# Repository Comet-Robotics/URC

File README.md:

# UTD University Rover Challenge

This is where all of our code and most of the project management will be base at.

## Overview

Discussions: Where all research topics will go and where you will log your ideas, progress, and questions at. I will also post research materials there too.

Issues: Once research is done we will create an issue for a topic and this is where you will contribute your code too and discuss issues that are arriving in the implementation.

## Instructions
- Start up the simulation and press play. 

- In another terminal, cd to rtab_package (such a dumb name we can definitely change this) which is in the ws_urc src folder, colcon build, source the install. 
- To run, "ros2 launch rtab_package rtab.launch.py". 
  - This node takes care of all transforms needed for the Nav2 stack.
  - rgbd odometry creates an odom -> base_link odometry message
  - ukf robot_localization fuses the IMU odometry with the visual odometry and publishes the odom -> base_link transformation
  - rgbd-slam publishes the map -> odom frame
  - RTAB-MAP frame to frame model
 
- Then, cd to navigation, which is also in the ws_urc src folder. Colcon build, source the install.
  - Run with "ros2 launch navigation nav.launch.py"
  - This initializes the nav2 stack, nothing outputs after initialization unless a goal is given
 
- Start rviz2
  - Set the global frame to "map"
  - include "Robot Description" topic to see the robot (the wheels dont move with it even though the transforms are being published, don't know what's going on there)
  - Include "odometry" topic, set ros2 topic to "odometry/filtered" to see the fused odometry
  - Include "/map" topic (this doesn't show up until nav2 is activated)
  - Include "goal pose" to see the given goal
  - Go to panels, click on navigation2. It should say the navigation is active. 
  - To send actions to the robot, in rviz, select 2d goal pose and place it on the map. Click Start Waypoint Navigation in the nav2 panel to start navigation

Install git 

git clone <github_uri>

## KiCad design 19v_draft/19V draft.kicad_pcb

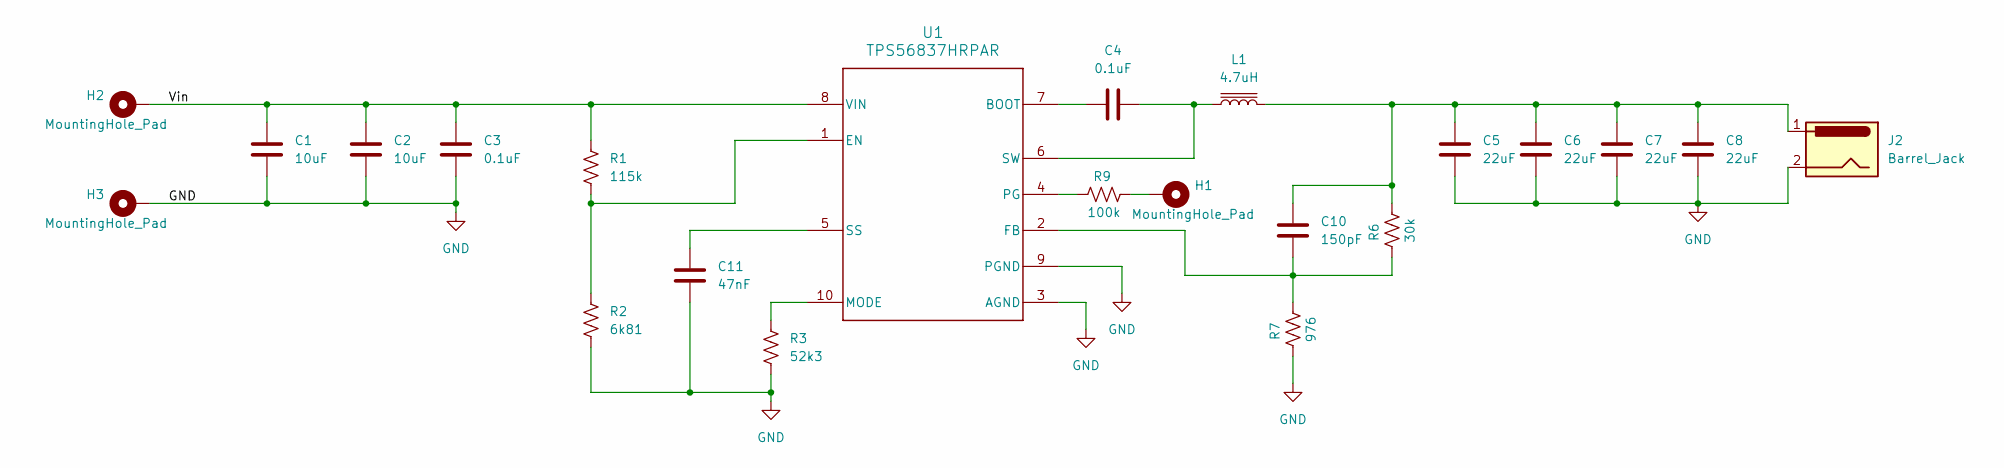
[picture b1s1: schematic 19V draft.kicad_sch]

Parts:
C1, C2: 10uF; C_0603_1608Metric
C3, C4: 0.1uF; C_0603_1608Metric
C5, C6, C7, C8: 22uF; C_0603_1608Metric
C10: 150pF; C_0603_1608Metric
C11: 47nF; C_0603_1608Metric
H1, H2, H3: MountingHole_Pad; MountingHole_2.5mm_Pad
J2: Barrel_Jack; BarrelJack_SwitchcraftConxall_RAPC10U_Horizontal
L1: 4.7uH; L_Abracon_ASPI-0630LR
R1: 115k; R_2512_6332Metric
R2: 6k81; R_2512_6332Metric
R3: 52k3; R_2512_6332Metric
R6: 30k; R_0805_2012Metric
R7: 976; R_2512_6332Metric
R9: 100k; R_0805_2012Metric
U1: TPS56837HRPAR; RPA0010A-MFG

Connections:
/Vin: C1.1, C2.1, C3.1, H2.1, R1.1, U1.8 (VIN)
GND: C1.2, C2.2, C3.2, C5.2, C6.2, C7.2, C8.2, C11.2, H3.1, J2.2, R2.2, R3.2, R7.1, U1.3 (AGND), U1.9 (PGND)
unnamed: C5.1, C6.1, C7.1, C8.1, C10.1, J2.1, L1.2, R6.2
unnamed: H1.1, R9.2
unnamed: C4.1, U1.7 (BOOT)
unnamed: R1.2, R2.1, U1.1 (EN)
unnamed: C10.2, R6.1, R7.2, U1.2 (FB)
unnamed: R3.1, U1.10 (MODE)
unnamed: R9.1, U1.4 (PG)
unnamed: C11.1, U1.5 (SS)
unnamed: C4.2, L1.1, U1.6 (SW)

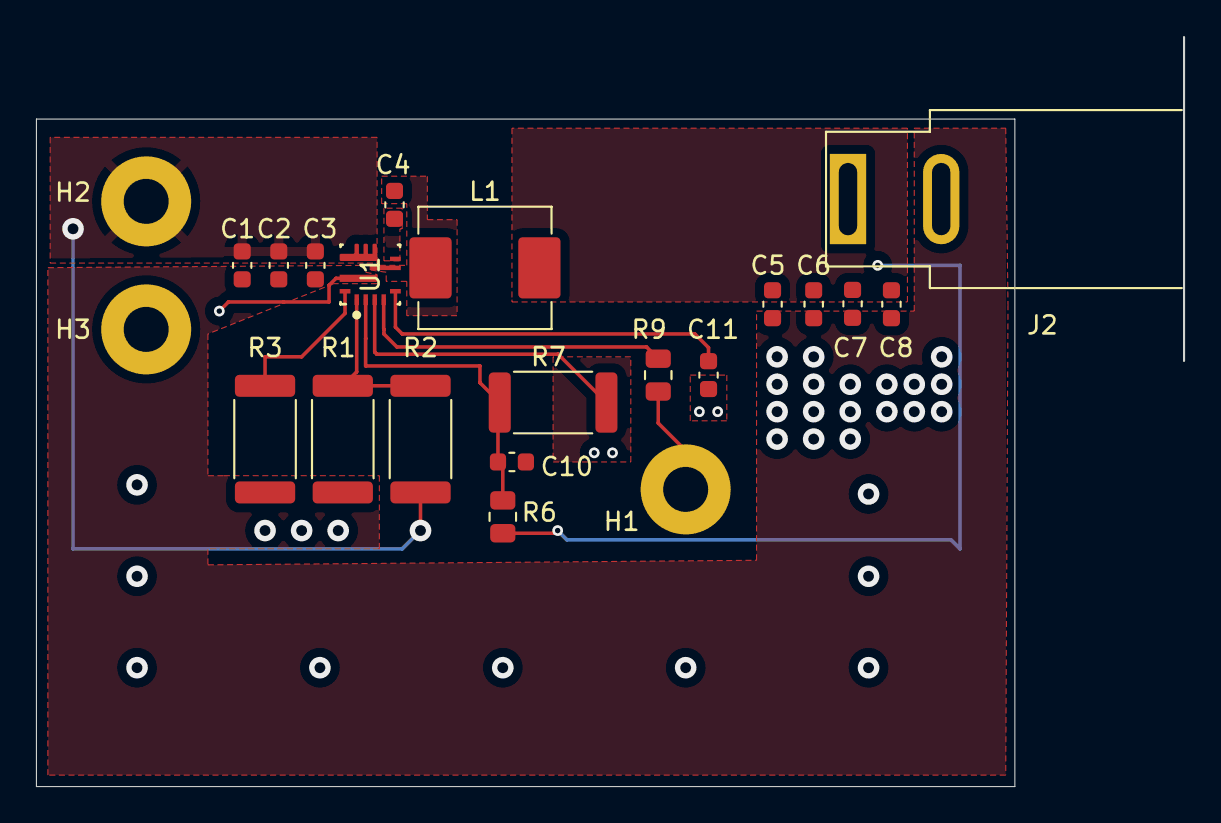
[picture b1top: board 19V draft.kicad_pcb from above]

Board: 4 copper layers, 63.7 x 41.6 mm, 22 parts (0 on the bottom side), 11 nets.

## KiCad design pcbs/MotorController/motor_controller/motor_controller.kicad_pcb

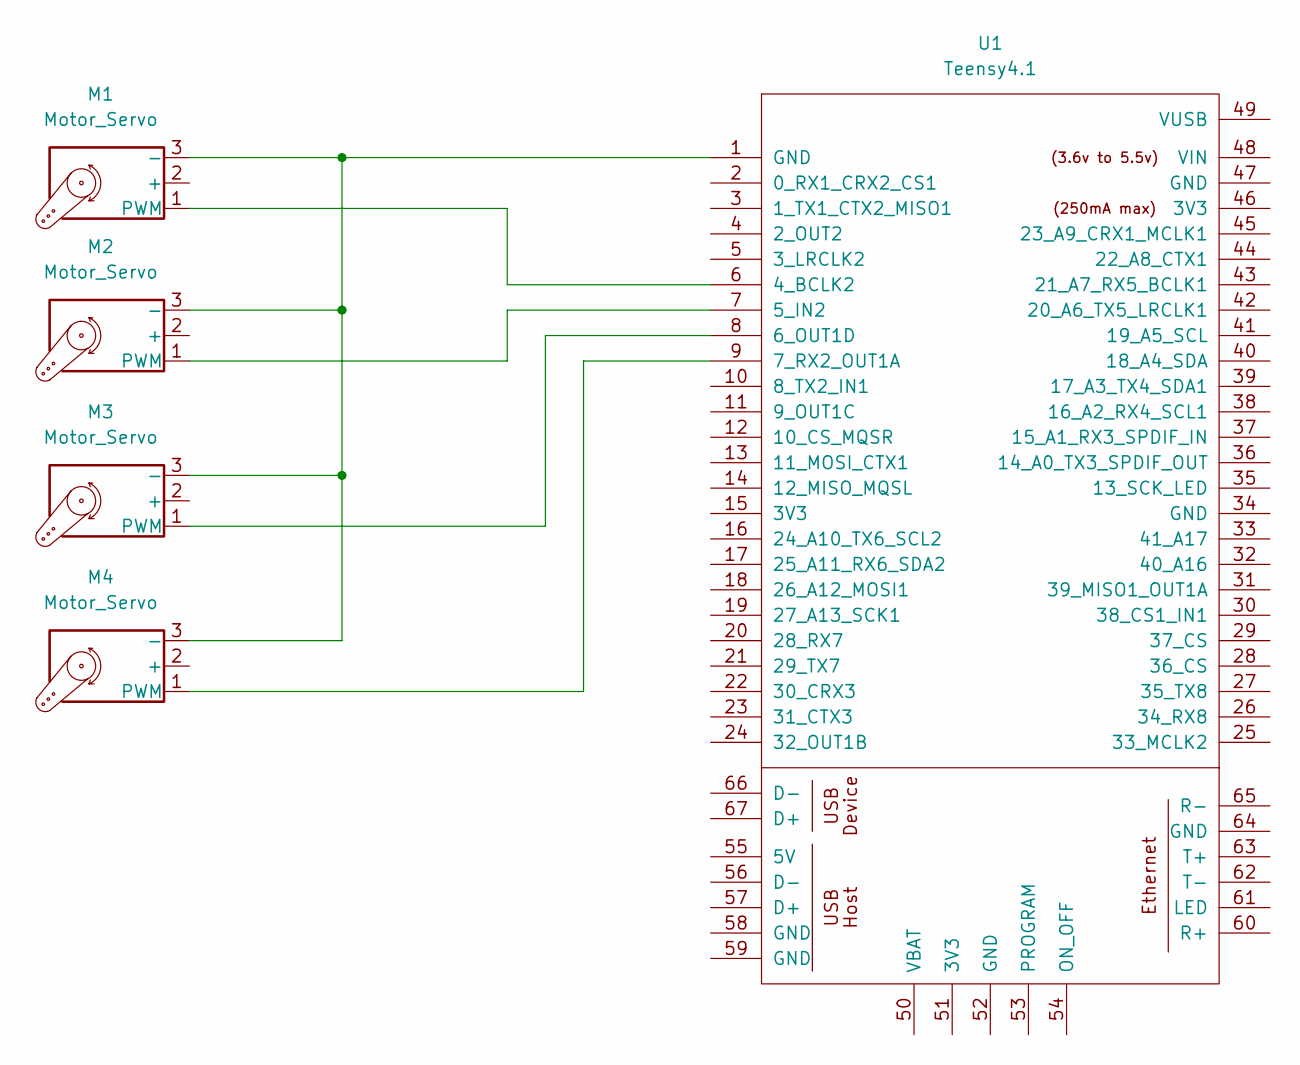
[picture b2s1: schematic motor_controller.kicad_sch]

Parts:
M1, M2, M3, M4: Motor_Servo; FanPinHeader_1x03_P2.54mm_Vertical
U1: Teensy4.1; Teensy41

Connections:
unnamed: M1.3 (-), M2.3 (-), M3.3 (-), M4.3 (-), U1.1 (GND)
unnamed: M1.1 (PWM), U1.6 (4_BCLK2)
unnamed: M2.1 (PWM), U1.7 (5_IN2)
unnamed: M3.1 (PWM), U1.8 (6_OUT1D)
unnamed: M4.1 (PWM), U1.9 (7_RX2_OUT1A)

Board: 2 copper layers, 5 parts (0 on the bottom side), 5 nets, no tracks yet.

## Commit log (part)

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2024-08-30 Update issue templates
2024-08-30 FEATURE: ROS2 EXPlain
2024-09-02 details
2024-09-04 Added Base Drivetrain Code
2024-09-04 house keeping
2024-09-04 added realsense-ros as submodule
2024-09-04 Flake
2024-09-04 Adding Nix Flaks
2024-09-05 Driver Update
2024-09-05 added flake deps for realsense
2024-09-06 auton_proj
2024-09-06 lil fix
2024-09-07 refactor
2024-09-07 renamed
2024-09-07 laying groundwork for ui
2024-09-09 UI Upgrades
2024-09-09 Fixed Arduino Code
2024-09-09 video streaming
2024-09-09 video streaming working multistreams
2024-09-12 asdasd
2024-09-14 Folder Movement
    Folder Movement
2024-09-17 Motor Driver Node
2024-09-19 Added forward and turn actions
2024-10-08 Added the alive message to drivetrain_node.py.
    Created new node for testing purposes. It's main
    function so far is to work on implementing button
    press readings to be able to control the rover from
    the terminal with w,a,s,d.
2024-10-09 Gazebo Simulation base
2024-10-10 README file and rm build folder
2024-10-10 Removed build folder
2024-10-10 Fixed Performance on large rocks
2024-10-11 Basic node for talking to sim and added sim stuff
2024-10-11 Obstac
2024-10-13 folder rename
2024-10-17 Added GPS Module
2024-10-17 Update readme for GPS
2024-11-05 3D Occupancy Mapping Using octomap_server
2024-11-05 3D occupancy grid node
2024-11-05 Pointcloud publishing
2024-11-05 more
2024-11-05 removing rover-ros
2024-11-05 tomato
2024-11-05 added back realsense-ros
2024-11-05 Video Stream works sub second latency
2024-11-05 Video Stream
2024-11-06 more ui stuff fixed some rtp forward issues
2024-11-06 + Basestation Link - Realsense Ros + VideoStreaming auto restart + Control over tcp
2024-11-06 + videostreaming + xbox control over tcp
2024-11-07 rover-ui updates
2024-11-07 restructure
2024-11-07 Migration to React + VIte
2024-11-08 setup localization launch file within occupancy_grid and imu and gps data outputs to /rover/imu and /rover/gps in ros2 now.
2024-11-09 added stepper
2024-11-11 progress
2024-11-11 fixed shty logging
2024-11-14 +fixed issues with fake and ffmpeg processes never ending
2024-11-19 wewe
2024-11-19 Add files via upload
    um does this work for the buck converter thing
2024-11-19 fixed issues w tcp
2024-11-19 imu node w/ rviz frame as child
2024-11-19 Publish transforms between sensors (transform from sensor to link is currently hard coded)
2024-11-19 port args to imu + readme update
2024-11-19 owef
2024-11-20 Cleaned up + Heartbeat
2024-11-20 Added usb ID
2024-11-20 Added hearbeat
2024-11-20 comments
2024-11-20 changed folder names
2024-12-03 Rotating to hell
2024-12-03 Working rotated map
2024-12-03 Getting there
2025-02-04 rgbd_odom, ekf robot_localization, rtabmap_slam, model.xacro file with correct transforms
2025-02-04 ekf.yaml and cleanup
2025-02-06 push
2025-02-06 Map Working
2025-02-08 Fixed Video Streaming added both and fixed some lagging
2025-02-09 Added IMU Vis
2025-02-10 Rtab-Map odometry improvements. Changed the strategy from Frame-to-Map to Frame-to-Frame. and updated the ekf filter to ignore vertical accelerations.
2025-02-10 cnanges
2025-02-10 nav2 implimentation with RTAB-MAP
2025-02-12 Added Reconnection to basestation node
2025-02-12 ReEnabled Controls from UI
2025-02-12 Cleaning up
2025-02-17 added basic go version of server needs webrtc
2025-02-18 work on receive function
2025-02-18 sending logic
2025-02-18 Removed go
2025-02-18 Added Dev Container
2025-02-18 added some better logging
2025-02-22 IMU Node
2025-02-22 Add 24v wiring harness
2025-02-26 oh my god it works. Updated camera in simulation to better model the realsense D435. Updated the state estimation filter to use ukf, instead of ekf. Configured the changes with rtabmap/Nav2.
2025-02-26 rviz config file in rtab_package/config
2025-02-26 config.rviz in rtab_package.config
2025-02-27 ARM SIM
2025-02-28 add basic light controller firmware
2025-02-28 Remove pycache files
2025-02-28 Initial radiodriver implementation
2025-02-28 kklj
2025-02-28 Receive messages over unix socket
2025-02-28 Standardize sleep time, readd source to proxy logs
2025-02-28 Add ham link to fake rover
2025-03-01 kjsdkfjsd
2025-03-01 Update radiodriver-proxy README
2025-03-01 Begin radio transmit stuff
2025-03-19 Add design breakdown and sequence diagram to README
2025-03-19 Explain purpose of shared queues
2025-03-19 Send received messages from radiodriver to other processes via Unix socket
2025-03-19 Begin serial line parsing method
2025-03-19 Handle empty frames gracefully
2025-03-19 Message unframing
2025-03-19 Switch to SimpleQueue for thread safety
2025-03-19 Switch serial buffer to bytearray
2025-03-19 Fix type
2025-03-19 Remove TODOs, update sequence diagram
2025-03-19 Revert unintended base station change
2025-10-28 added legacy dependencies, add explanatory comments, updated site navigation
2025-11-06 Cleaned up
2025-11-06 Cleaned up Zone Identifier files
2025-11-06 Updated gitignore
2025-11-06 Upadted dependencies
2025-11-06 Updated file paths
2025-11-06 Fixed dependencies
2025-11-06 Fixed file paths
2025-11-06 Updated dependencies
2025-11-10 Cleaned up some comments
2025-11-10 Updated image_publisher to get its video source from a parameter
2025-11-11 Added a battery component (in progress)
2025-11-11 Started testing Gazebo
2025-11-13 Added basic code for gazebo
2025-11-18 added headers for different site pages
2025-11-19 Added a ReadMe
2025-11-19 Updated to avoid using hard coded variable values in favor of using parameters
2025-11-20 started new UI, set up react project
2025-11-20 Fix Documentation
2025-11-20 more dependencies :(((
2025-11-20 added dependency for typescript
2025-11-20 added dependency for typescript (the previous push was me deleting an image i messed up 😭)
2025-11-20 added folders for pages and for components
2025-11-20 added gyroscope file
2025-11-20 created seperate pages and links for homepage, science payload and gyroscope
2025-11-21 started adding header styles, deleted extra text
2025-11-26 Updated simulation in line with gazebo harmonic
2025-11-29 Added Spectrometer functionality and custom interfaces package
2025-11-29 Documentation for GPUX and IMU
2025-11-30 Documentation for GPUX and IMU
    Updated descriptions and formatting for clarity in the README.
2025-12-02 Document `rtab_package`
2025-12-02 Guess who made a Navbar workinggit add .! - J
2025-12-02 spectrometer calibration update
2025-12-02 Added a header and card file for future use - JC
2025-12-02 added temp_sensor arduino code
2025-12-02 fixed css on header, added headers to other pages, imported new fonts, made new class for nav bar
2025-12-02 fixed spacing on nav bar, changed fonts/general apperance of UI
2025-12-02 added seperator line on science & gyroscope pages
2025-12-09 New componentsgit add .
2025-12-12 added arm_moveit to src
2025-12-25 Added a lighter world and launch file for testing purposes
2025-12-25 Reduced the update rate of both cameras from 90 Hz to 5, massively speeding up sim while remaining fast enough for testing purposes
2025-12-25 Added robot description package and integrated sim package within main workspace. Also added microros agent packages
2026-01-14 THESE NOTIFICATIONS GONNA DRIVE ME INSANE - J
2026-01-14 changing color theme - z
2026-01-15 changing color scheme again - z
2026-01-22 fixing text colors
2026-01-22 UI changes, adding more content blocks
2026-01-22 got rid of card and am still working on notif - J
2026-01-22 fixing notifs - J
2026-01-22 trying to ovrwrite bad changes - z
2026-01-22 Navigation and GPS
2026-02-02 added notification button to nav bar
2026-02-04 motor driver code for teensy
2026-02-05 added nav bar icons for connectivity & battery
2026-02-05 I MADE THE NOTIFICATIONS WORKgit add .git add . - J
2026-02-05 Got a battery popup working too
2026-02-05 set placeholders for video stream components on homepage
2026-02-05 funny comment
2026-02-05 combined branches for notifs and video stream placeholders
2026-02-06 changes to motor driver todo: work on encoders
2026-02-08 Wifi Popup and Battery Popup online (no styling yet) - J
2026-02-09 encoder driver updated (probably, but i suspect many an error)
2026-02-09 Pin changes and bug fixes for motor driver
2026-02-09 added a header to video streams + reorganized css alphabetically
2026-02-10 Got rid of excess stuff
2026-02-10 Footer added - J
2026-02-10 addineg space for hyperspec camera on science payload page
2026-02-10 Timer front set up (working on backend) - J
2026-02-10 changes in the format of the timer and added comments - J
2026-02-12 added camera feeds and used tester url to check
2026-02-12 fixed positioning of battery & connection pop ups and notification bar css
2026-02-12 fixed notif side bar to align with the nav bar
2026-02-12 fixed header appearance, background of video streams
2026-02-12 changed css of footer, fon, color, gen appearance
2026-02-12 moved the documentation into its own folder
2026-02-15 Motor Test Code update for 6 motors
2026-02-15 Motor code fix
2026-02-18 Update pin assignments and print encoder pin state
2026-02-19 Fix encoder state printing
2026-02-20 working on gyroscpe visualizer
2026-02-20 spec data, sensor data, battery update
2026-02-20 Rewrote MotorTest to utilize microros
2026-02-20 Cleaned up code to make it more readable
2026-02-21 fixed some bugs and tested on leds
2026-02-21 Added raman spectrometer (TODO: calibration)
2026-02-22 Added direction changing logic. Tested on LEDs
2026-02-23 Pin updates
2026-02-23 pin update pt 2
2026-02-24 changed styling of block
2026-02-24 changed styling again
2026-02-24 minor chnages and bug fixes
2026-02-24 Untested; Updated to support Skid Steering.
2026-02-25 Fixed a bug where negative PWM could be sent to the ESC
2026-02-25 Minor changes
2026-02-25 Temporarily removed buggy breaking logic
2026-02-25 Reversing is stupid
2026-02-25 feat: init steering controller project
2026-02-25 feat: testing arduino code
2026-02-26 more style changes
2026-02-26 change footer styling
2026-02-26 feat: update pinout
2026-02-26 feat: step motor on loop
2026-02-27 feat: re add all steppers
2026-02-27 checkpoint
2026-02-27 ckpt
2026-02-27 Added Ackermann style steering and updated controller code
2026-02-28 Updated PWM pins for motors
2026-03-25 Added WIP Yolo stuff, WIP datasets
2026-04-07 Minor Bug Fix
2026-04-17 [Untested] Rewrote motor code. Handles Skid steering.
2026-04-17 Minor Bug fixes
2026-04-17 Bug fixes and debug code added
2026-04-17 Added a ros package that splits the pwm and rpm messages into left and right.
2026-04-17 Added a simple control system to make both sides' motors reach the same target PWM at the same time.
2026-04-21 Updated pins.
2026-04-30 Add up to date arm urdf package
